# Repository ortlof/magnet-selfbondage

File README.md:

# Lock ME-UP
A Magnet-Based Self bondage Time Lock

## Overview:
1. Electrical Parts
2. 3D Printed Parts
3. Mechanical Parts
4. PCB & Routing
5. Firmware
6. Assembly

### 1. Electrical Parts

The Bondage Lock Uses following Parts:

1x LILYGO TTGO T1 ESP32
1x Keeppower 18650 3400mAh (Protected)
1x 1A Micro USB 18650   https://www.amazon.de/TECNOIOT-Lithium-Battery-Charging-Charger/dp/B07T52KGDT
1x MT3608 DC-DC Netzteil 
1x MOSFET N-CH IRL1404ZPBF-ND
1x DIODE ARRAY GP BYV32-200-E3/45GI-ND
1x 10k Resistor
1x Power Switch
1x Button (with LED)
1x Jack Socket Mono
1x Jack Plug Mono
1x Some Kables
1x Magent 500-700 N 12V DC

### 2. 3D Printed Parts

Check Folder Case for STL & STEP Files. All parts can be printed without Support.

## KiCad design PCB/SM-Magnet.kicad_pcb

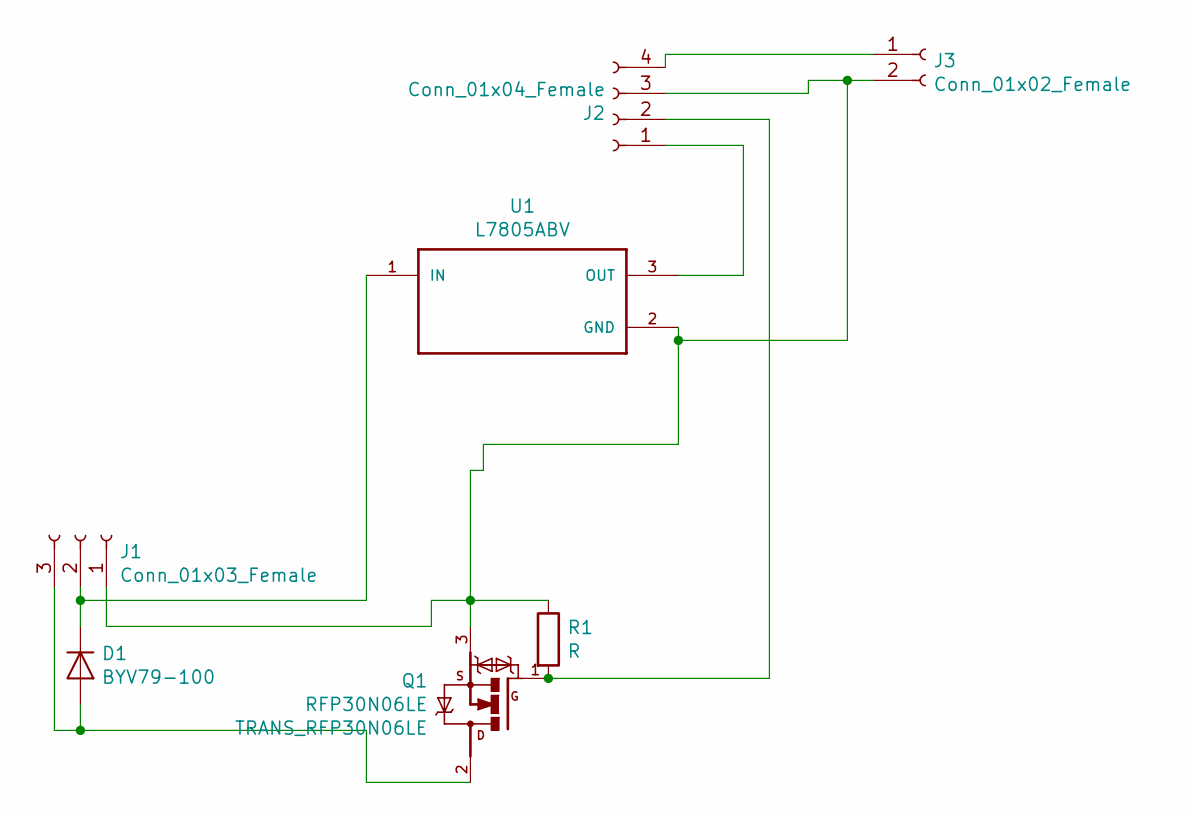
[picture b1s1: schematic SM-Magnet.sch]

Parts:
D1: BYV79-100; TO254P1053X483X1985-3
J1: Conn_01x03_Female; JST_XH_B3B-XH-A_1x03_P2.50mm_Vertical
J2: Conn_01x04_Female; JST_XH_B4B-XH-A_1x04_P2.50mm_Vertical
J3: Conn_01x02_Female; JST_XH_B2B-XH-A_1x02_P2.50mm_Vertical
Q1: RFP30N06LE; TRANS_RFP30N06LE
R1: R; R_Box_L8.4mm_W2.5mm_P5.08mm
U1: L7805ABV; TO254P460X1020X1945-3P

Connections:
unnamed: D1.1 (K), J1.2, U1.1 (IN)
unnamed: D1.2 (A), J1.3, Q1.2 (D)
unnamed: J1.1, J2.3, J3.2, Q1.3 (S), R1.1, U1.2 (GND)
unnamed: J2.1, U1.3 (OUT)
unnamed: J2.2, Q1.1 (G), R1.2
unnamed: J2.4, J3.1

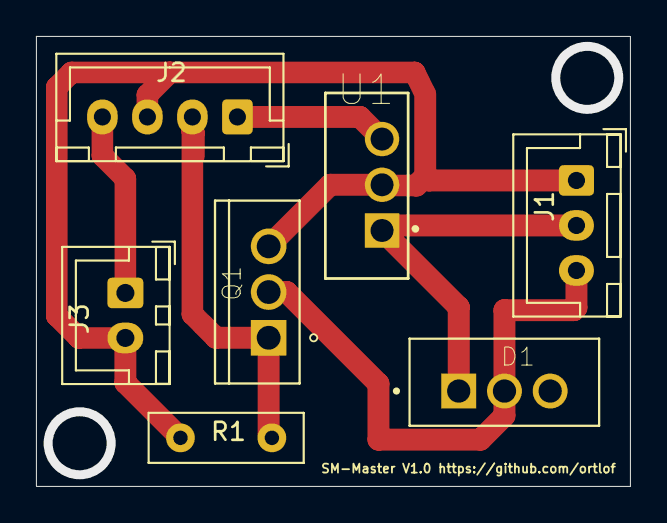
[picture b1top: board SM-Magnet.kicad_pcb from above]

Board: 2 copper layers, 33.0 x 25.0 mm, 7 parts (0 on the bottom side), 6 nets.

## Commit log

2020-03-24 V1.0
    Stand allone Version no Wifi
2020-04-07 V1.1 Wifi & Standalone
2020-06-14 V.1.2
    Final Wifi Features
2020-06-14 Test Readme
2021-02-23 V.1.3
2021-07-31 V.1.4
    Added Features - Changed Webpage to Responsive
2021-08-01 v.1.5
    Changed webapp with menü
2021-10-16 Add Battery Masurement
2022-01-18 V.1.7
2022-01-18 V.1.8
    Added 3D Print Files Case
2022-01-18 Readme Update
